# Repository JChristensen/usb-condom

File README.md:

# USB Condom
https://github.com/JChristensen/usb-condom  
README file  
Jack Christensen Feb-2018

## Overview
A little something for the tinfoil hat crowd. Amaze your friends, confound your enemies, spread FUD far and wide or just have a good laugh.

This is just my implementation of a concept that's been around for a while. The idea is that USB charging ports in public places (airport kiosks, hotels, coffee shops, etc.) should be considered untrusted because it's possible they could contain technology that attempts to access data on mobile devices plugged in for charging. The USB Condom prevents this because it passes the power through but not the USB data lines. Just pop it on the end of any USB cable and you're practicing safe charging! From what I can tell, there are almost no documented instances of such a thing actually occurring. There might have been a [demonstration at DEF CON.](https://krebsonsecurity.com/2011/08/beware-of-juice-jacking/) So mostly this is just a fun project, but hey, it can't hurt, right?

PC boards can be ordered [from OSH Park](https://www.oshpark.com/shared_projects/0s1QDkyq).
A bill of materials is available [at Mouser Electronics](https://www.mouser.com/ProjectManager/ProjectDetail.aspx?AccessID=3e867db098) and also in this repo.

## CC BY-SA
"USB Condom" by Jack Christensen is licensed under [CC BY-SA 4.0](https://creativecommons.org/licenses/by-sa/4.0/).

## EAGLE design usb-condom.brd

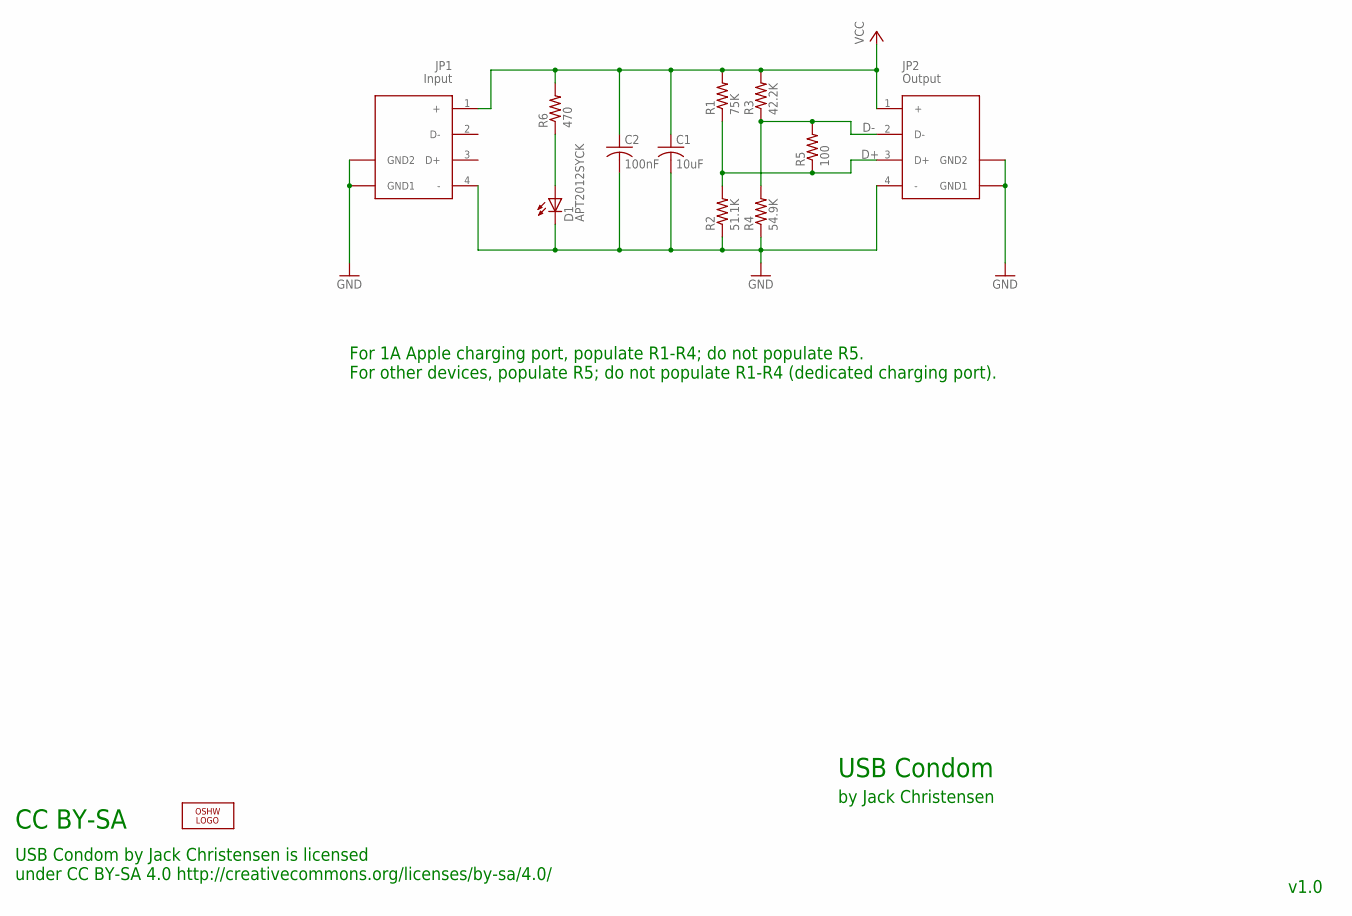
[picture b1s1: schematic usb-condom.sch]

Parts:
C1: 10uF; M0805
C2: 100nF; M0805
D1: APT2012SYCK; M0805
JP1: Input; UP2-AH-X-TH
JP2: Output; USB-A-S-RA-ADAMTECH
LOGO1: OSHW_LOGO_8MILX0100-NT; OSHW_8X100_NOTEXT
R1: 75K; M0805
R2: 51.1K; M0805
R3: 42.2K; M0805
R4: 54.9K; M0805
R5: 100; M0805
R6: 470; M0805

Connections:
D+: JP2.3 (D+), R1.1, R2.2, R5.1
D-: JP2.2 (D-), R3.1, R4.2, R5.2
GND: C1.2, C2.2, D1.2 (C), JP1.4 (-), JP1.P$5 (GND1), JP1.P$6 (GND2), JP2.4 (-), JP2.GND1, JP2.GND2, R2.1, R4.1
unnamed: D1.1 (A), R6.1
VCC: C1.1, C2.1, JP1.1 (+), JP2.1 (+), R1.2, R3.2, R6.2

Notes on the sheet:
USB Condom
by Jack Christensen
v1.0
CC BY-SA
USB Condom by Jack Christensen is licensed under CC BY-SA 4.0 http://creativecommons.org/licenses/by-sa/4.0/
For 1A Apple charging port, populate R1-R4; do not populate R5. For other devices, populate R5; do not populate R1-R4 (dedicated charging port).

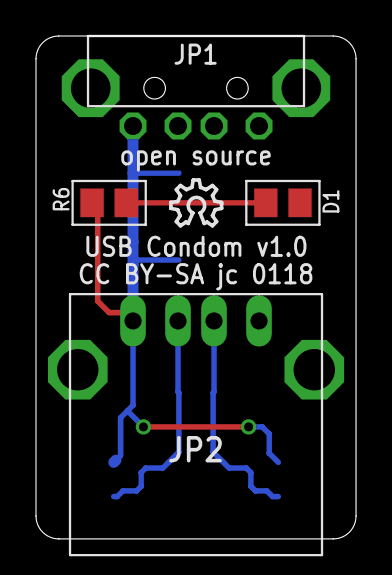
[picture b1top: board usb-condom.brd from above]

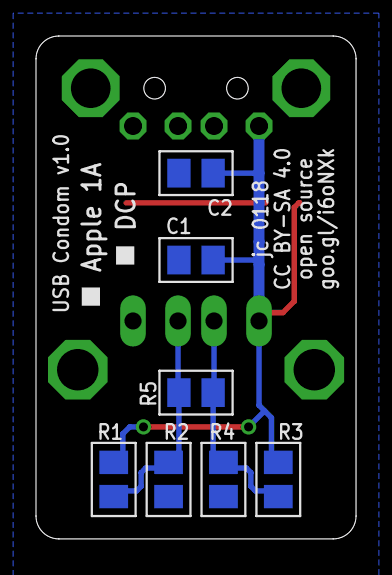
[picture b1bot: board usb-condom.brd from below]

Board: 2 copper layers, 17.8 x 27.9 mm, 12 parts (7 on the bottom side), 5 nets.

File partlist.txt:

Partlist

Exported from usb-condom.sch at 2/15/2018 12:25 PM

EAGLE Version 7.5.0 Copyright (c) 1988-2015 CadSoft

Assembly variant: 

Part     Value          Device     Package             Library  Sheet

C1       10uF           C-USM0805  M0805               _jc      1
C2       100nF          C-USM0805  M0805               _jc      1
D1       APT2012SYCK    LEDM0805   M0805               _jc      1
JP1      Input          UP2-AH-TH  UP2-AH-X-TH         _jc      1
JP2      Output         USB-A      USB-A-S-RA-ADAMTECH _jc      1
R1       75K            R-US_M0805 M0805               _jc      1
R2       51.1K          R-US_M0805 M0805               _jc      1
R3       42.2K          R-US_M0805 M0805               _jc      1
R4       54.9K          R-US_M0805 M0805               _jc      1
R5       100            R-US_M0805 M0805               _jc      1
R6       470            R-US_M0805 M0805               _jc      1

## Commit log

2018-02-15 Initial commit.

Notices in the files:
usb-condom.brd:
CC BY-SA jc 0118
